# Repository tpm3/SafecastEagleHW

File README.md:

SafeCastHW
==========

Dedicated repository for SafeCast HW (EAGLE) libraries and designs.

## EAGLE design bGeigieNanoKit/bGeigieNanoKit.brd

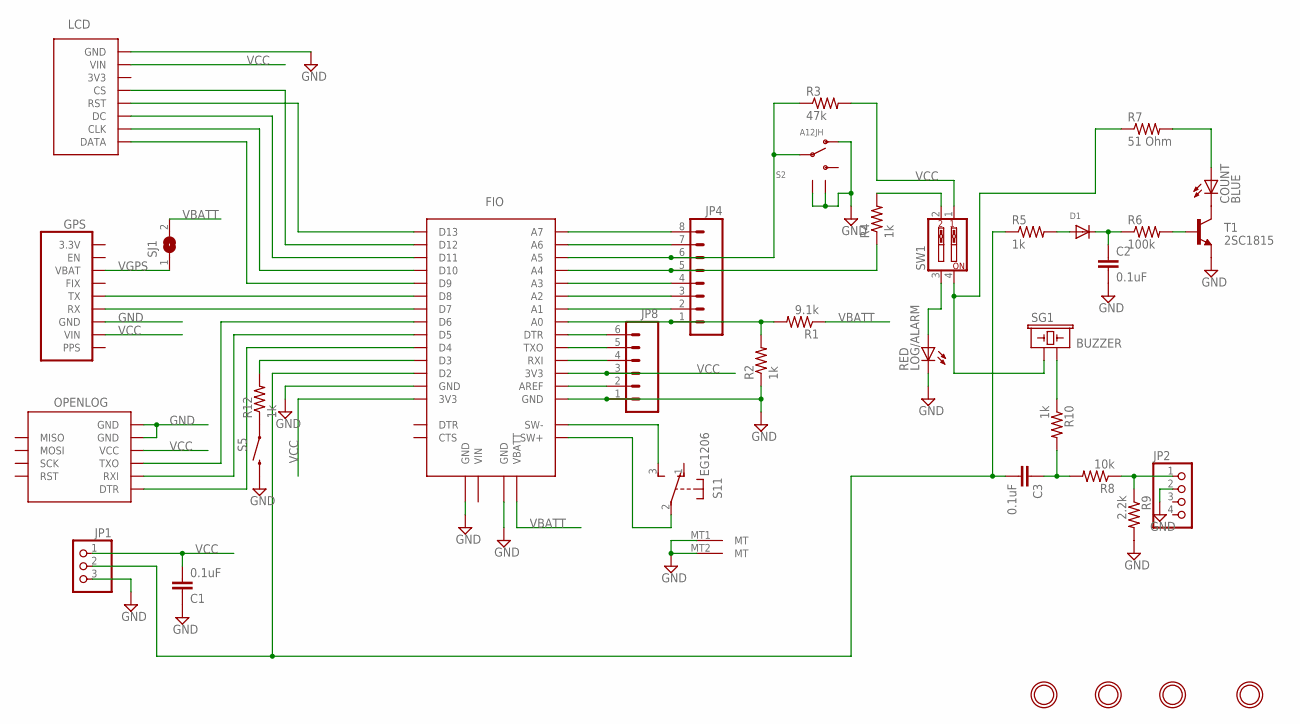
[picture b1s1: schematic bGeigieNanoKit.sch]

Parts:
C1, C2, C3: 0.1uF; C025-024X044
COUNT: BLUE; LED3MM
D1: DIODEDO-1N4148; DO-1N4148
FIO: FIO_SOCKETBOT; FIO_V23_SOCKET_BOT
GPS: ULTIMATE_GPSTOP; ULTIMATE_GPS_V3_TOP
JP1: PINHD-1X3/90; 1X03/90
JP2: HEADER-1X4ROUND; 1X04_ROUND
JP4: M081X08; 1X08
JP8: M06SIP; 1X06
LCD: SSD1306_128X64_V2_LCD1.3IN_LEVER; SSD1306_128X64_1.3IN_LCD_LEVER
LOG/ALARM: RED; LED3MM
OPENLOG: OPENLOG
R1: 9.1k; 0207/10
R2, R4, R5, R10, R12: 1k; 0207/10
R3: 47k; 0207/10
R6: 100k; 0207/10
R7: 51 Ohm; 0207/10
R8: 10k; 0207/10
R9: 2.2k; 0207/10
S1: EG1206
S2: A12JH; A12AH
S5: SWITCH-MOMENTARY-2PTH; TACTILE-PTH
SG1: BUZZER; BUZZER-12MM
SJ1: SOLDERJUMPERCLOSED; SOLDERJUMPER_CLOSEDWIRE
SW1: SW_DIP-2; EDG-02
T1: 2SC1815; TO92-ECB
U$6, U$7, U$8, U$9: MOUNTINGHOLE3.0THIN; MOUNTINGHOLE_3.0_PLATEDTHIN

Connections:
GND: C1.1, C2.2, FIO.JP1$2 (GND), FIO.JP2$1 (GND), FIO.JP5$1 (GND), FIO.JP6$1 (GND), GPS.JP1$3 (GND), GPS.U$8$P$1 (GND), GPS.U$9$P$1 (GND), JP1.3, JP2.2, JP8.1, LCD.JP1$8 (GND), LCD.U$23$P$1 (GND), LCD.U$26$P$1 (GND), LOG/ALARM.K (C), OPENLOG.JP1$5 (GND), OPENLOG.JP1$6 (GND), R2.1, R9.2, S1.MT1 (MT), S1.MT2 (MT), S2.P$1, S2.P$4 (GND), S2.P$5 (GND), S5.3 (2), T1.E
unnamed: FIO.JP1$10 (D9), LCD.JP1$1 (DATA)
unnamed: FIO.JP1$11 (D10), LCD.JP1$2 (CLK)
unnamed: FIO.JP1$12 (D11), LCD.JP1$3 (DC)
unnamed: FIO.JP1$13 (D12), LCD.JP1$5 (CS)
unnamed: FIO.JP1$14 (D13), LCD.JP1$4 (RST)
unnamed: FIO.JP1$9 (D8), GPS.JP1$5 (TX)
unnamed: FIO.JP1$8 (D7), GPS.JP1$4 (RX)
unnamed: FIO.JP1$7 (D6), OPENLOG.JP1$3 (TXO)
unnamed: FIO.JP1$6 (D5), OPENLOG.JP1$2 (RXI)
unnamed: FIO.JP1$5 (D4), OPENLOG.JP1$1 (DTR)
unnamed: FIO.JP5$7 (A0), JP4.1, R1.2, R2.2
unnamed: FIO.JP7$2 (SW+), S1.2
unnamed: FIO.JP7$1 (SW-), S1.3 (S)
unnamed: FIO.JP5$12 (A5), JP4.6, R3.1, S2.P$2
unnamed: FIO.JP5$13 (A6), JP4.7
unnamed: LOG/ALARM.A, SW1.3
unnamed: R4.2, SW1.2
unnamed: C3.2, FIO.JP1$3 (D2), JP1.2, R5.1
unnamed: COUNT.A, R7.2
unnamed: R12.1, S5.1
unnamed: COUNT.K (C), T1.C
unnamed: R10.1, SG1.- (2)
unnamed: C3.1, R8.2, R10.2
unnamed: JP2.1, R8.1, R9.1
unnamed: D1.A, R5.2
unnamed: C2.1, D1.C, R6.1
unnamed: R6.2, T1.B
unnamed: FIO.JP1$4 (D3), R12.2
unnamed: R7.1, SG1.+ (1), SW1.4
unnamed: FIO.JP5$11 (A4), JP4.5, R4.1
unnamed: FIO.JP5$10 (A3), JP4.4
unnamed: FIO.JP5$9 (A2), JP4.3
unnamed: FIO.JP5$8 (A1), JP4.2
unnamed: FIO.JP5$6 (DTR), JP8.6
unnamed: FIO.JP5$5 (TXO), JP8.5
unnamed: FIO.JP5$4 (RXI), JP8.4
unnamed: FIO.JP5$2 (AREF), JP8.2
unnamed: FIO.JP5$14 (A7), JP4.8
VBATT: FIO.JP2$2 (VBATT), R1.1, SJ1.2
VCC: C1.2, FIO.JP1$1 (3V3), FIO.JP5$3 (3V3), GPS.JP1$2 (VIN), JP1.1, JP8.3, LCD.JP1$7 (VIN), OPENLOG.JP1$4 (VCC), R3.2, SW1.1
VGPS: GPS.JP1$7 (VBAT), SJ1.1

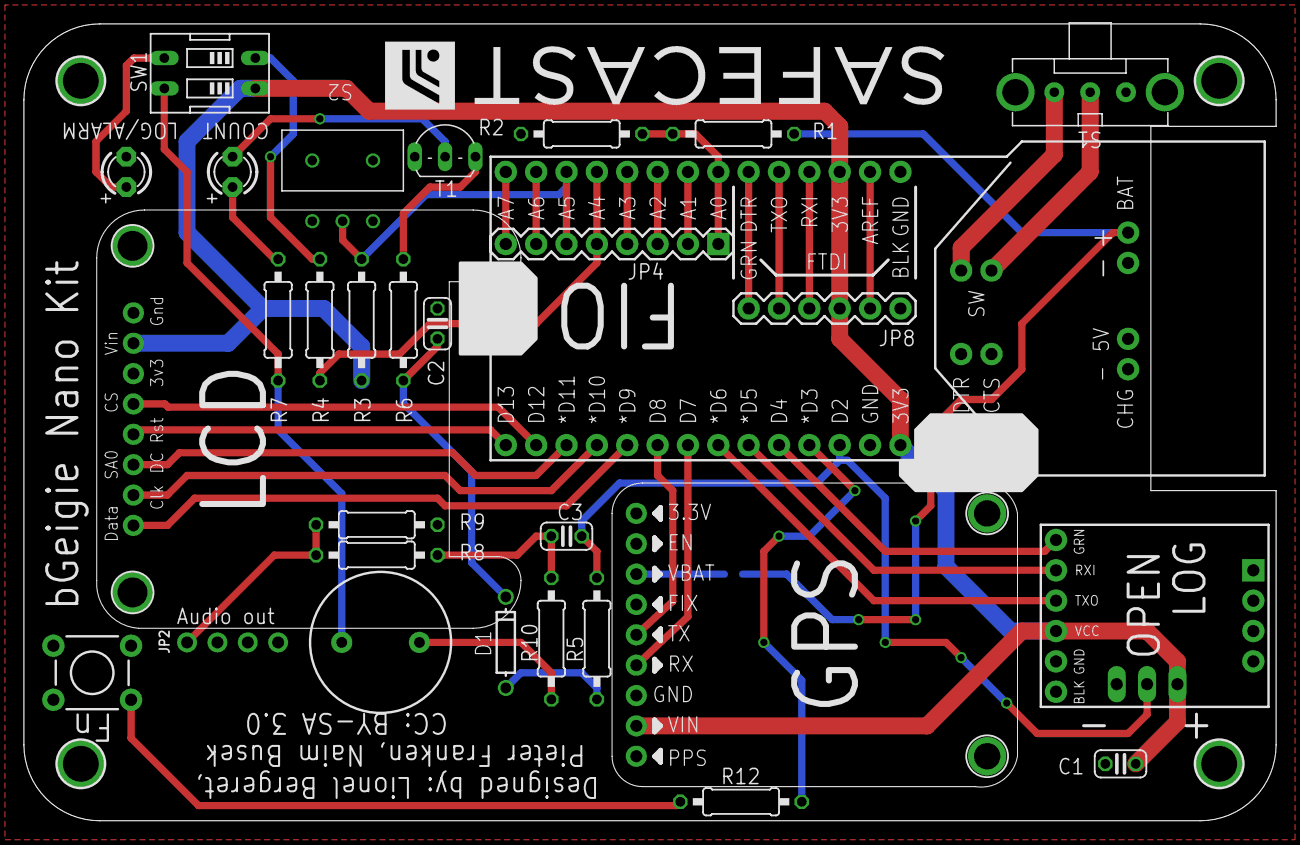
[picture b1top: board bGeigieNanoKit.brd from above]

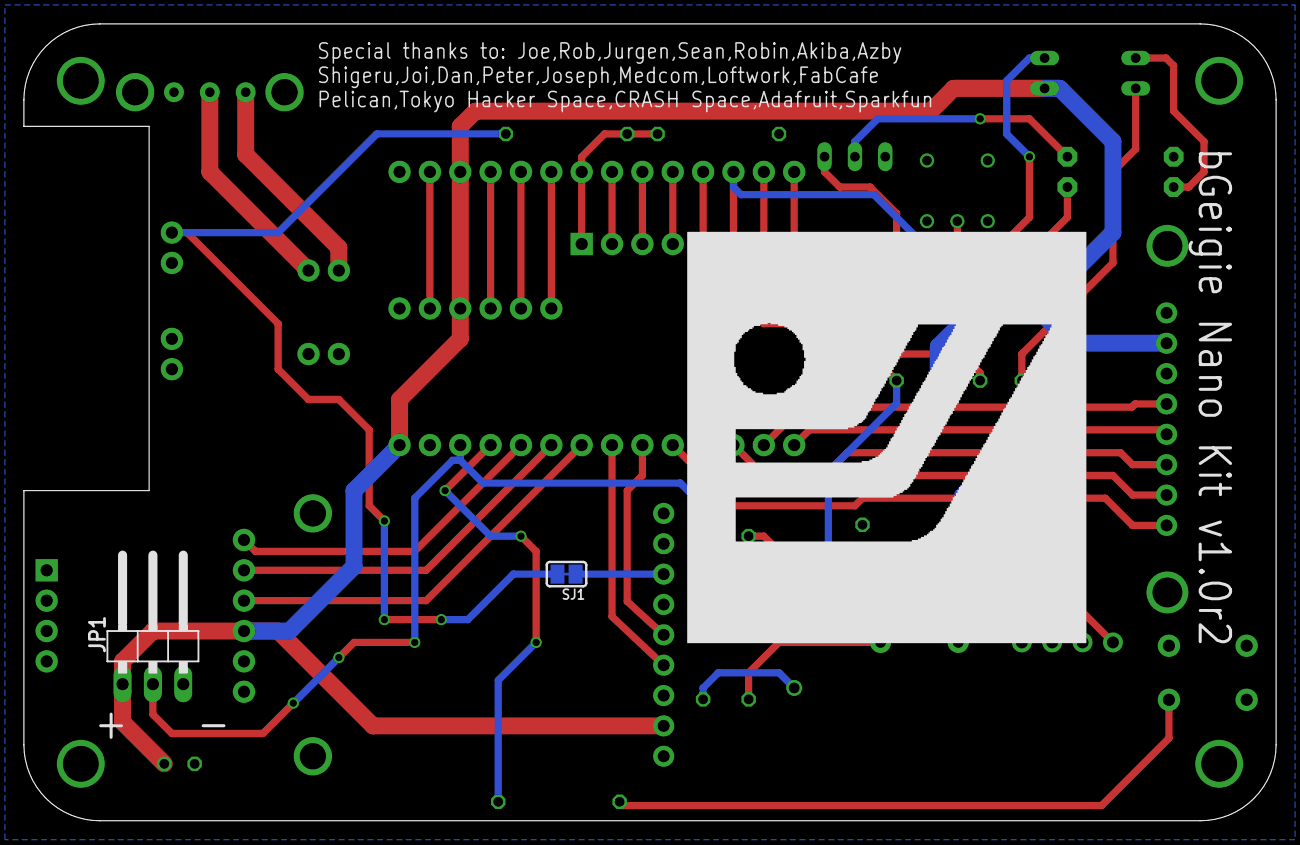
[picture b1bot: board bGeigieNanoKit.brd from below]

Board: 2 copper layers, 104.8 x 66.7 mm, 38 parts (4 on the bottom side), 42 nets.

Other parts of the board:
U$1: SAFECAST_LOGO4
U$5: SAFECAST_LOGO2

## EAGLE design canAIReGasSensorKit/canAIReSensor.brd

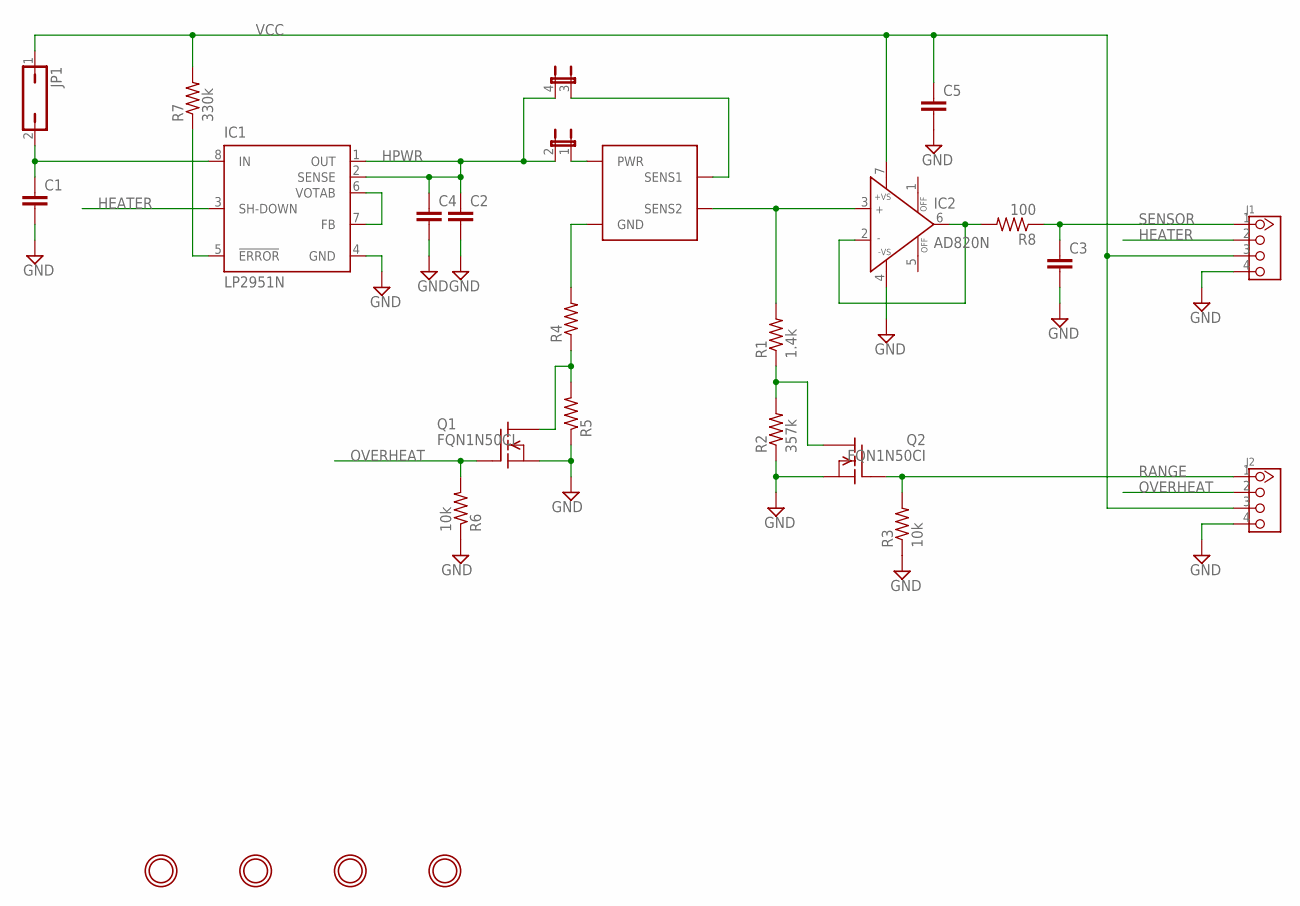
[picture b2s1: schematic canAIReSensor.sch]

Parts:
C1, C2, C3, C4, C5: C-EU050-024X044; C050-024X044
IC1: LP2951N; DIL08
IC2: AD820N; DIL08
J1, J2: TWIG-4P-2.0'90D'; 4P-2.0-90D
JP1: JP1Q; JP1
JP4: JP2QE; JP2Q
Q1, Q2: FQN1N50CI; TO92-INLINE
R1: 1.4k; 0204/7
R2: 357k; 0204/7
R3, R6: 10k; 0204/7
R4, R5: R-US_0204/7; 0204/7
R7: 330k; 0204/7
R8: 100; 0204/7
U$1: E2V_MICS
U$2, U$3, U$4, U$5: MOUNTINGHOLE2.5; MOUNTINGHOLE_2.5_PLATED

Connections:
GND: C1.2, C2.2, C3.2, C4.2, C5.2, IC1.4 (GND), IC2.4 (-VS), J1.4, J2.4, Q1.3 (S), Q2.3 (S), R2.1, R3.1, R5.1, R6.1
HEATER: IC1.3 (SH-DOWN), J1.2
HPWR: C2.1, C4.1, IC1.1 (OUT), IC1.2 (SENSE), JP4.2, JP4.4 (2)
unnamed: Q2.1 (D), R1.1, R2.2
unnamed: R4.2, U$1.1 (GND)
unnamed: JP4.1, U$1.3 (PWR)
unnamed: IC1.6 (VOTAB), IC1.7 (FB)
unnamed: C1.1, IC1.8 (IN), JP1.2
unnamed: Q1.1 (D), R4.1, R5.2
unnamed: IC1.5 (!ERROR), R7.1
unnamed: IC2.2 (IN-), IC2.6 (OUT), R8.2
OVERHEAT: J2.2, Q1.2 (G), R6.2
RANGE: J2.1, Q2.2 (G), R3.2
S1: JP4.3 (1), U$1.4 (SENS1)
S2: IC2.3 (IN+), R1.2, U$1.2 (SENS2)
SENSOR: C3.1, J1.1, R8.1
VCC: C5.1, IC2.7 (+VS), J1.3, J2.3, JP1.1, R7.2

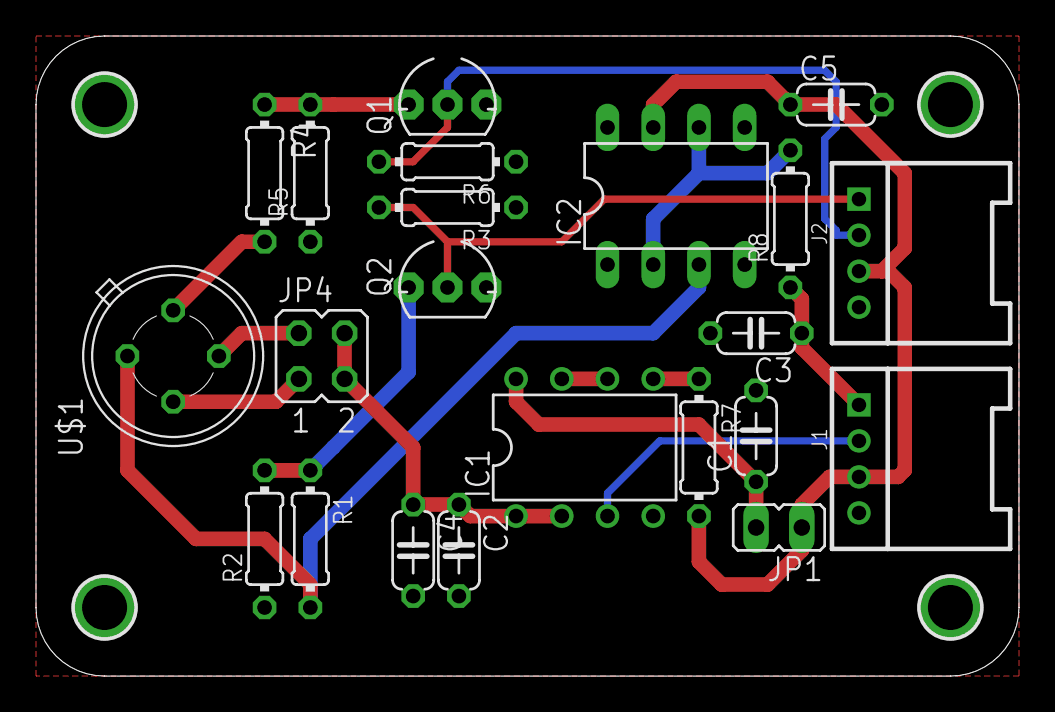
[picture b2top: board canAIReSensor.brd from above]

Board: 2 copper layers, 54.6 x 35.6 mm, 26 parts (0 on the bottom side), 17 nets.

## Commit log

2012-10-17 library updated with full module footprints. test components removed. board updated to use new library components.
2012-10-19 updated library footprints with single/double sided options. preliminary component placement on board to verify fit.
2012-10-24 full set of components added to library. initital placement of all components.
2012-10-29 increasing width of outlines. moving outlines place layers
2012-10-29 resize board to be better fit in case. did inital pass at routing.
2012-10-30 fully routed board
2012-10-31 cleaned up final routing
2012-10-31 cleaning up libs and updating brd
2012-10-31 smashing all parts and moving labels to be visable adding current limit resistor for charge led add lables to leds
2012-11-06 adding v2 version of the board with a single LCD
2012-11-06 gererating outputs for single OLED layout. changigng to toggle switch
2012-12-18 updating with current (not hacked) footprints for gps and LCD
2012-12-24 commiting all changes for what should be Release v1.0
2012-12-24 updating readme to reflect current files
2012-12-24 changing color to blue/white
2012-12-28 updated mechanical model files
2012-12-28 adding manufacturing files for production of v1.0
2012-12-28 removing .asm file from zip since gmail refuses to email it claiming it is an executable.
2013-01-30 initial commit of Safecast Air gas sensor
2013-01-30 adding readme
2013-01-30 removing seeedstudio main site link to avoid confusion
2013-01-30 fixing naming to append kit (convention for through hole designs)
2013-01-30 moved files to new subdirectory
2013-02-05 moving .gitignore to top level to apply to all projects
2013-02-05 adding footprint for e2v gas sensor
2013-02-05 initial routing compleated
2013-02-05 minor changes to CAM config
2013-02-05 moving configuration files to a common location
2013-02-05 moving more configuration files to a common location
2013-02-05 adding script to bundle files for fab
2013-02-05 adding fabrication files
2013-02-05 increasing isolation and rounding the corners
2013-02-15 bundled for fab
2013-03-28 before removing second lcd
2013-03-28 applied most all changes rc v1.0r2
2013-04-03 adding shielded switch EG1206
2013-04-03 finishing change set for rev2
2013-04-03 adding more space between irover plug and post
2013-04-03 updated fabrication files for pcb rev2
2013-04-03 removing mechanical model for yellow pcb
2013-04-03 updated mechanical model for rev2
2013-04-03 finishing drc approvals for rev2
2013-04-03 merging hardware development from personal fork into main repo
2013-04-03 removing copied libs to replace with tracked ones
2013-04-06 Changed R8 to 47k and and R9 to 4.7k and fixed some overlaying text.
2013-04-06 Revert "Changed R8 to 47k and and R9 to 4.7k and fixed some overlaying text."
    This reverts commit f053eba477d0c686d0d0ac7e4f314e797ef1138b.
2013-04-08 final changes and output files for Rev. 2
2013-04-08 adding final version of library for rev 2
2013-04-08 approving errors/warnings on schematic

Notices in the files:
parts and their libraries:
microbuilder: This work is placed in the public domain, and may be freely used for commercial and non-commercial work with the following conditions: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
SparkFun: Licensing: CC v3.0 Share-Alike You are welcome to use this library for commercial purposes.
